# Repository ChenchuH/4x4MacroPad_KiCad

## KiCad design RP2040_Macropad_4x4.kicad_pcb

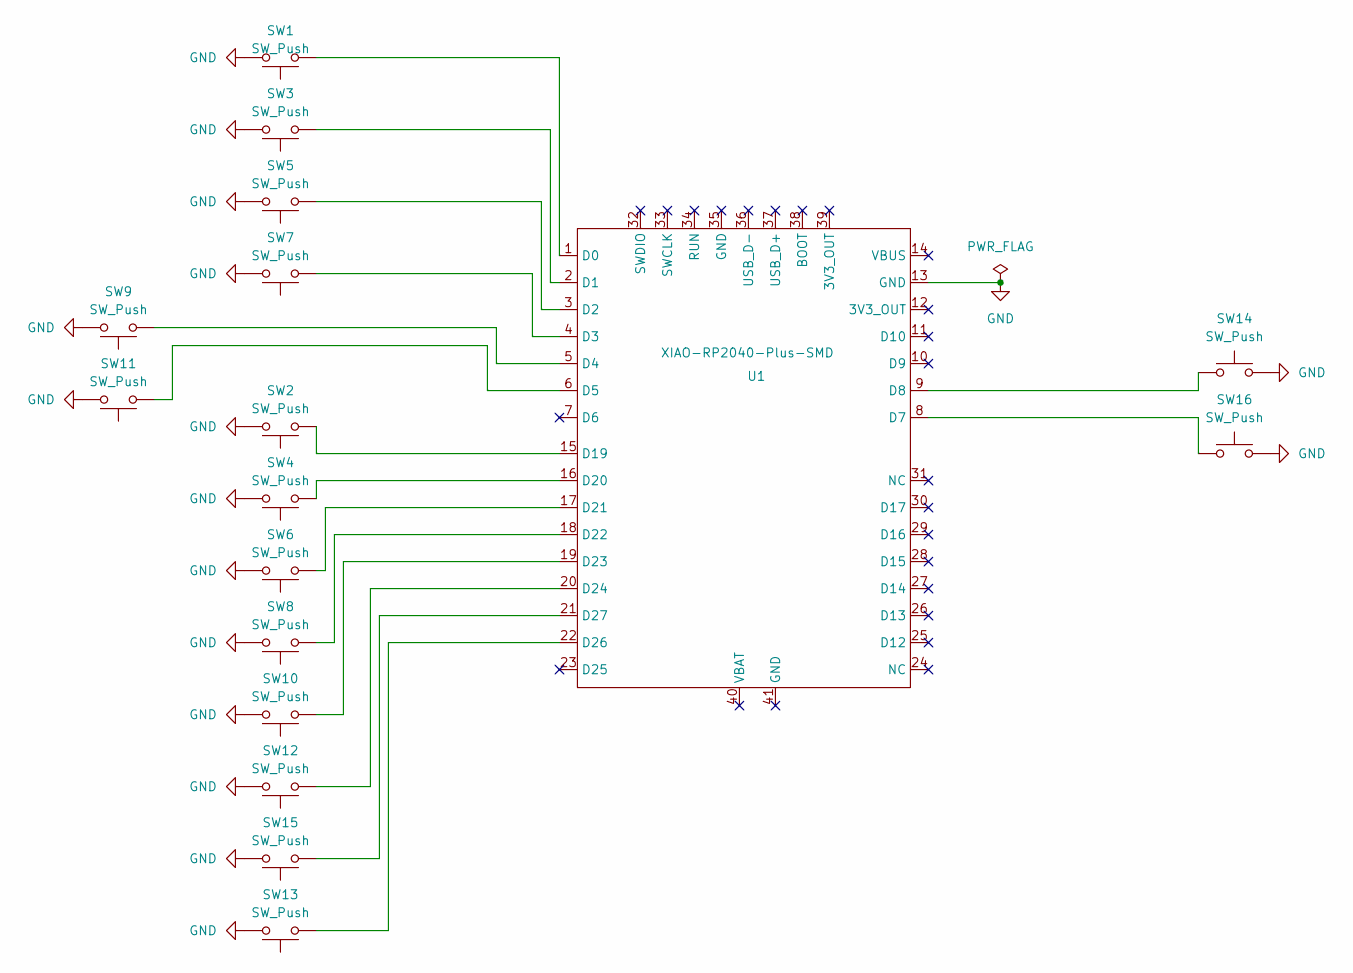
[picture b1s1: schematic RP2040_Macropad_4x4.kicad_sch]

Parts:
SW1, SW2, SW3, SW4, SW5, SW6, SW7, SW8, SW9, SW10, SW11, SW12, SW13, SW14, SW15, SW16: SW_Push
U1: XIAO-RP2040-Plus-SMD

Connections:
GND: SW1.2, SW2.2, SW3.2, SW4.2, SW5.2, SW6.2, SW7.2, SW8.2, SW9.2, SW10.2, SW11.2, SW12.2, SW13.2, SW14.2, SW15.2, SW16.2, U1.13 (GND)
unnamed: SW1.1, U1.1 (D0)
unnamed: SW3.1, U1.2 (D1)
unnamed: SW5.1, U1.3 (D2)
unnamed: SW7.1, U1.4 (D3)
unnamed: SW9.1, U1.5 (D4)
unnamed: SW11.1, U1.6 (D5)
unnamed: SW16.1, U1.8 (D7)
unnamed: SW14.1, U1.9 (D8)
unnamed: SW2.1, U1.15 (D19)
unnamed: SW4.1, U1.16 (D20)
unnamed: SW6.1, U1.17 (D21)
unnamed: SW8.1, U1.18 (D22)
unnamed: SW10.1, U1.19 (D23)
unnamed: SW12.1, U1.20 (D24)
unnamed: SW13.1, U1.22 (D26)
unnamed: SW15.1, U1.21 (D27)

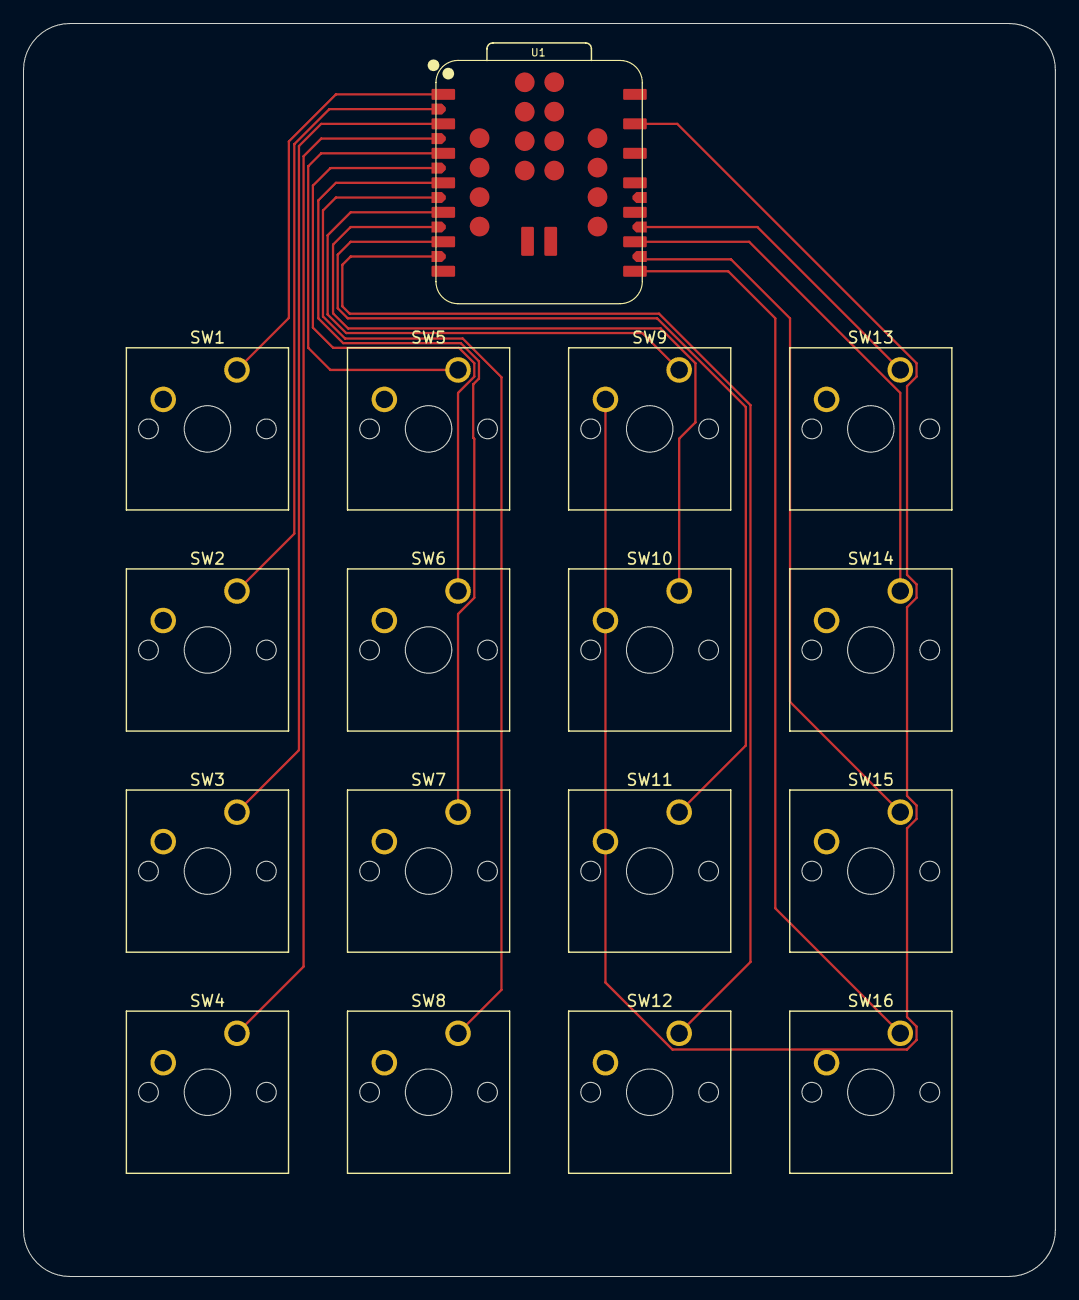
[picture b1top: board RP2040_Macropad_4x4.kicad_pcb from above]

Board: 2 copper layers, 88.9 x 107.9 mm, 17 parts (0 on the bottom side), 17 nets.
